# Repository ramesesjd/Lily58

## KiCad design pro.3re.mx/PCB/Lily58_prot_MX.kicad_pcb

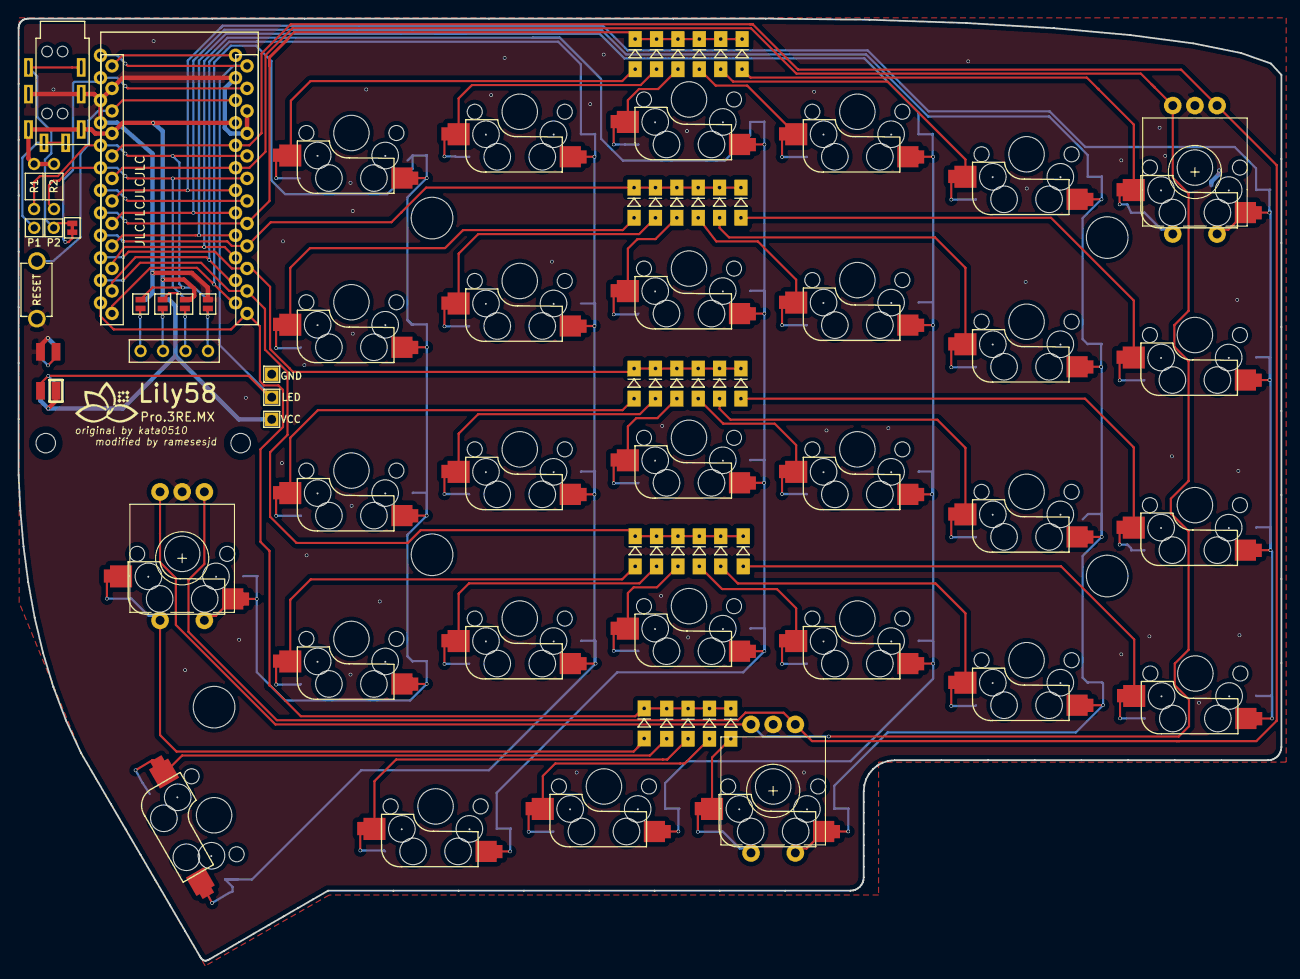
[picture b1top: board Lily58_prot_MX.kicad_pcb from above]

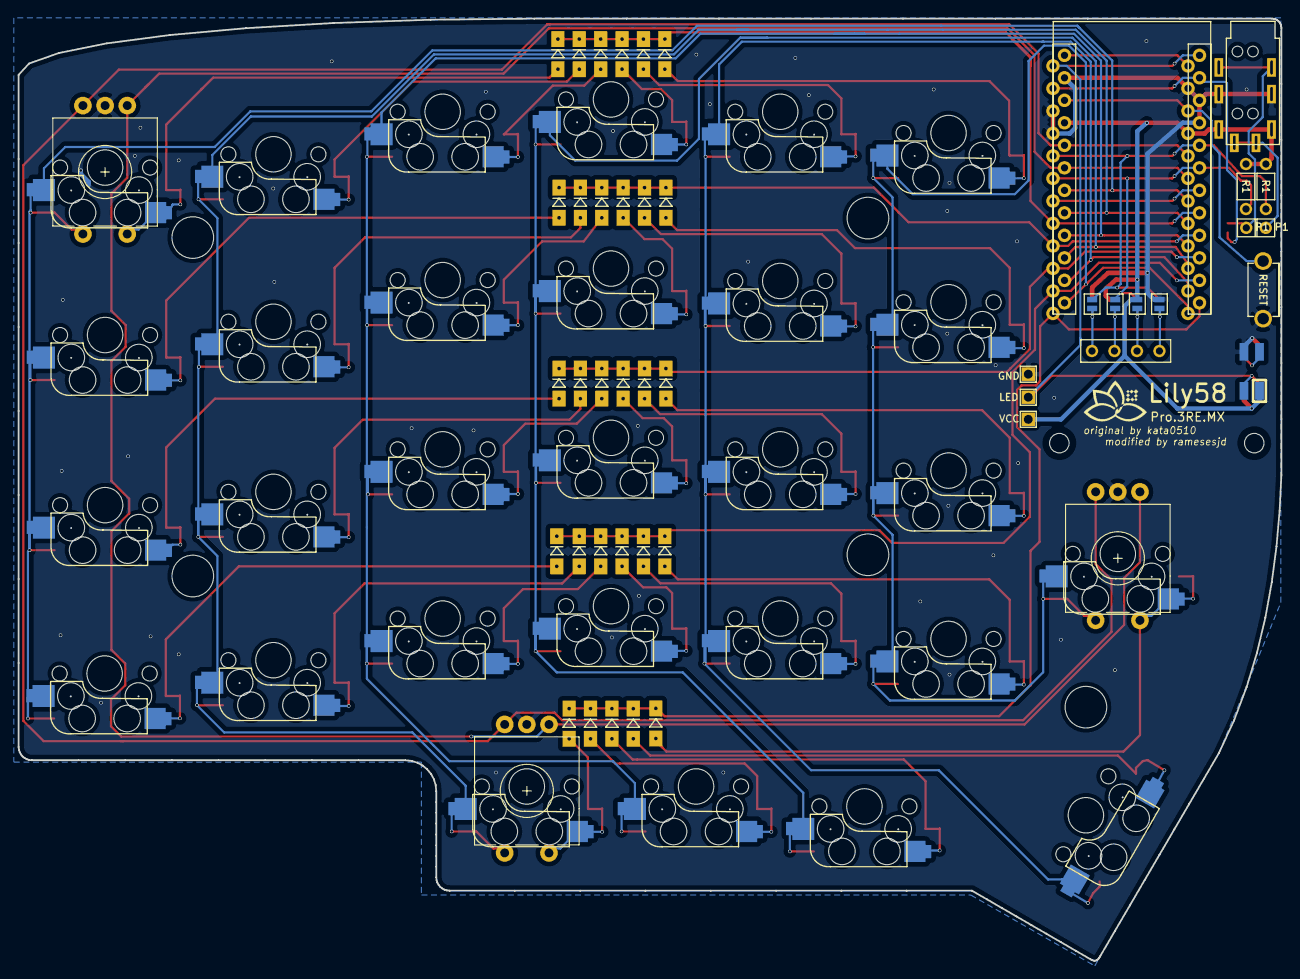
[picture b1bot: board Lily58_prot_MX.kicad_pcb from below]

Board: 2 copper layers, 142.5 x 106.3 mm, 87 parts (33 on the bottom side), 55 nets.

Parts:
D1, D2, D3, D4, D5, D6, D7, D8, D9, D10, D11, D12, D13, D14, D15, D16, D17, D18, D19, D20, D21, D22, D23, D24, D25, D26, D27, D28, D29: D; Diode_SOD123
J1: LED
J2: 4PIN; MJ-4PP-9
J3: OLED; OLED_4Pin
JP1, JP2, JP3, JP4, JP5, JP6, JP7, JP8: Jumper_NO_Small; Jumper
L1: SK6812MINI; SK6812MINI_underglow_rev
P1, P2: i2c_pin; 1pin_conn
R1, R2: R; RESISTOR_mini
RSW1: SW_RST; TACT_SWITCH_TVBP06
SW1, SW2, SW3, SW4, SW5, SW6, SW7, SW8, SW9, SW10, SW11, SW12, SW13, SW14, SW15, SW16, SW17, SW18, SW19, SW20, SW21, SW22, SW23, SW24, SW25, SW26, SW27, SW28, SW29: SW_PUSH; MX_Hotswap
SW30, SW31, SW32: ROT_ENC_SW; RotaryEncoder_Alps_EC11E-Switch_Vertical_H20mm-keebio_modif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
TH1, TH2: HOLE; HOLE_M2
TH3, TH4, TH5, TH6, TH7: HOLE; HOLE_M2_TH
U1: ProMicro; ProMicro_rev2
W1: jumper; jumper_data

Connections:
DATA: U1.2, W1.1
GND: J1.3, J2.2, JP1.2, JP8.2, L1.2, RSW1.1, SW30.C, SW31.C, SW32.C, U1.3, U1.4, U1.23
LED: J1.2, L1.3, U1.1
unnamed: D1.2, SW1.2
unnamed: D2.2, SW2.2
unnamed: D3.2, SW3.2
unnamed: D4.2, SW4.2
unnamed: D5.2, SW5.2
unnamed: D7.2, SW7.2
unnamed: D8.2, SW8.2
unnamed: D9.2, SW9.2
unnamed: D10.2, SW10.2
unnamed: D11.2, SW11.2
unnamed: D12.2, SW12.2
unnamed: D13.2, SW13.2
unnamed: D14.2, SW14.2
unnamed: D15.2, SW15.2
unnamed: D16.2, SW16.2
unnamed: D17.2, SW17.2
unnamed: D18.2, SW18.2
unnamed: D19.2, SW19.2
unnamed: D20.2, SW20.2
unnamed: D21.2, SW21.2
unnamed: D22.2, SW22.2
unnamed: D23.2, SW23.2
unnamed: D24.2, SW24.2
unnamed: D26.2, SW26.2
unnamed: D27.2, SW27.2
unnamed: D28.2, SW28.2
unnamed: J2.3, P2.1, W1.2
unnamed: J2.4, P1.1
unnamed: J3.1, JP4.1, JP8.1
unnamed: J3.2, JP3.1, JP7.1
unnamed: J3.3, JP2.1, JP6.1
unnamed: J3.4, JP1.1, JP5.1
R1_SW1: D25.2, SW25.2, SW30.S1
R1_SW2: SW1.1, SW7.1, SW13.1, SW19.1, SW25.1, SW30.S2, U1.13
R2_SW1: D29.2, SW29.2, SW31.S1
R2_SW2: SW5.1, SW11.1, SW17.1, SW23.1, SW29.1, SW31.S2, U1.17
R3_SW1: D6.2, SW6.2, SW32.S1
R3_SW2: SW6.1, SW12.1, SW18.1, SW24.1, SW32.S2, U1.18
RESET: RSW1.2, U1.22
R_A: SW30.A, SW31.A, SW32.A, U1.20
R_B: SW30.B, SW31.B, SW32.B, U1.19
SCL: JP3.2, JP6.2, R2.2, U1.6
SDA: JP4.2, JP5.2, R1.2, U1.5
VCC: J1.1, J2.1, JP2.2, JP7.2, L1.4, R1.1, R2.1, U1.21
col2: SW4.1, SW10.1, SW16.1, SW22.1, SW28.1, U1.16
col3: SW3.1, SW9.1, SW15.1, SW21.1, SW27.1, U1.15
col4: SW2.1, SW8.1, SW14.1, SW20.1, SW26.1, U1.14
row0: D1.1, D2.1, D3.1, D4.1, D5.1, D6.1, U1.8
row1: D7.1, D8.1, D9.1, D10.1, D11.1, D12.1, U1.9
row2: D13.1, D14.1, D15.1, D16.1, D17.1, D18.1, U1.10
row3: D19.1, D20.1, D21.1, D22.1, D23.1, D24.1, U1.11
row4: D25.1, D26.1, D27.1, D28.1, D29.1, U1.12

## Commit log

2020-09-15 Add Pro Rev2
2020-12-29 created prot-mx files and modified
2020-12-29 fixed slikscreen labels on PCB (VCC and GND for LEDs swapped to match pad labels) and prettified traces
2020-12-29 added ToDo list
2020-12-29 added critical step #4 to ToDo list
2020-12-29 fixed mistake in ToDo list
2020-12-30 re-saved after experimenting with adding MP holes back to encoder footprint
2020-12-31 mv prot-mx to p-rot3-mx
2020-12-31 added extra encoders to schematic and PCB -- still need to be routed; diodes now SOD
2021-01-01 added routing for GND to all encoders
2021-01-02 added test file
2021-01-02 new branch; updated to-do
2021-01-02 deleted test file
2021-01-02 rerouted all switch, encoder, and ground traces
2021-01-03 added Lily58Glow led footprint to folder
2021-01-03 renamed folder to be consistent with branch names
2021-01-03 updated todo
2021-01-04 LEDs added to schematic; switch footprints flippped; tracks deleted; rerouting started
2021-01-04 modified SK6812 footprint to include cutout
2021-01-09 repositioned diodes, using original LED footprints
2021-01-09 replaced hotswap footprint with TH footprint where encoder footprint overlaps
2021-01-10 removed per-key-LEG in favour of underglow only
2021-01-11 routing nearly complete; some ground pads need connecting
2021-01-17 grouped diodes and re-routed all switch traces; considering removing underglow in favour of single top-mounted layer indicating LED
2021-01-23 keeping only 1 LED as indicator and fixed all remaining unconnected traces
2021-01-24 minor rerouting for greater ground plane coverage; also moved bottow row diodes to be centred with upper row diodes.
2021-01-24 added modified Lily58 silkscreen logo to board; generated gerber files as per JLC instructions.
2021-01-24 changed folder name
2021-01-26 removed todo.txt
2021-01-30 removed test file
